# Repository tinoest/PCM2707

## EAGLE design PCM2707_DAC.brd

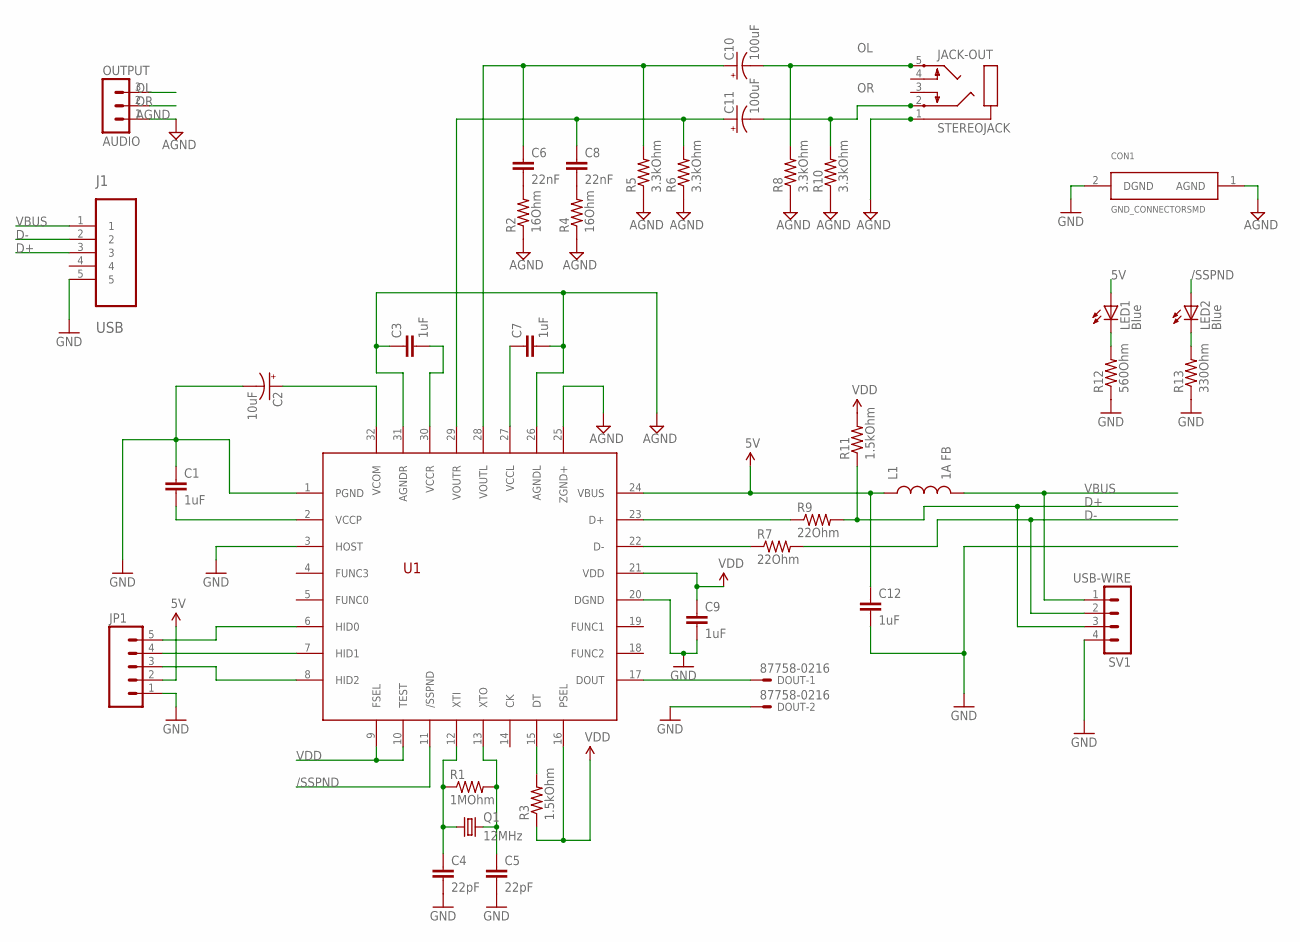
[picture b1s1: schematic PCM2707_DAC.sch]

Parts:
C1, C3, C7, C9, C12: 1uF; 0805
C2: 10uF; PANASONIC_C
C4, C5: 22pF; 0805
C6, C8: 22nF; 1210
C10, C11: 100uF; PANASONIC_D
CON1: GND_CONNECTORSMD; GND_CONNECTOR
DOUT: 87758-0216
J1: USB; MOLEX_47346-0001
JACK-OUT: STEREOJACK; STX3100
JP1: M05LOCK; 1X05_LOCK
L1: 1A FB; 0805
LED1, LED2: Blue; LED-0603
OUTPUT: AUDIO; MA03-1
Q1: 12MHz; HC49U-V
R1: 1MOhm; 0805
R2, R4: 16Ohm; 0805
R3, R11: 1.5kOhm; 0805
R5, R6, R8, R10: 3.3kOhm; 0805
R7, R9: 22Ohm; 0805
R12: 560Ohm; 0805
R13: 330Ohm; 0805
SV1: USB-WIRE; MA04-1
U1: PCM2707C_TQFP32"; 32TQFP_PCM2707C

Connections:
5V: C12.1, JP1.2, L1.1, LED1.A, U1.24 (VBUS)
/SSPND: LED2.A, U1.11 (/SSPND)
AGND: C3.1, C7.2, CON1.1 (AGND), JACK-OUT.1, OUTPUT.1, R2.1, R4.1, R5.1, R6.1, R8.1, R10.1, U1.25 (ZGND+), U1.26 (AGNDL), U1.31 (AGNDR)
D+: J1.3, R9.2, R11.1, SV1.3
D-: J1.2, R7.2, SV1.2
GND: C1.1, C2.-, C4.2, C5.2, C9.2, C12.2, CON1.2 (DGND), DOUT.2, J1.5, JP1.1, R12.1, R13.1, SV1.4, U1.1 (PGND), U1.3 (HOST), U1.20 (DGND)
unnamed: JP1.5, U1.6 (HID0)
unnamed: C1.2, U1.2 (VCCP)
unnamed: JP1.4, U1.7 (HID1)
unnamed: C2.+, U1.32 (VCOM)
unnamed: JP1.3, U1.8 (HID2)
unnamed: DOUT.1, U1.17 (DOUT)
unnamed: C4.1, Q1.1, R1.1, U1.12 (XTI)
unnamed: C5.1, Q1.2, R1.2, U1.13 (XTO)
unnamed: R9.1, U1.23 (D+)
unnamed: R7.1, U1.22 (D-)
unnamed: C3.2, U1.30 (VCCR)
unnamed: LED1.C, R12.2
unnamed: R3.2, U1.15 (DT)
unnamed: C7.1, U1.27 (VCCL)
unnamed: C8.2, R4.2
unnamed: C6.2, R2.2
unnamed: C8.1, C11.+, R6.2, U1.29 (VOUTR)
unnamed: LED2.C, R13.2
unnamed: C6.1, C10.+, R5.2, U1.28 (VOUTL)
OL: C10.-, JACK-OUT.5, OUTPUT.3, R8.2
OR: C11.-, JACK-OUT.2, OUTPUT.2, R10.2
VBUS: J1.1, L1.2, SV1.1
VDD: C9.1, R3.1, R11.2, U1.9 (FSEL), U1.10 (TEST), U1.16 (PSEL), U1.21 (VDD)

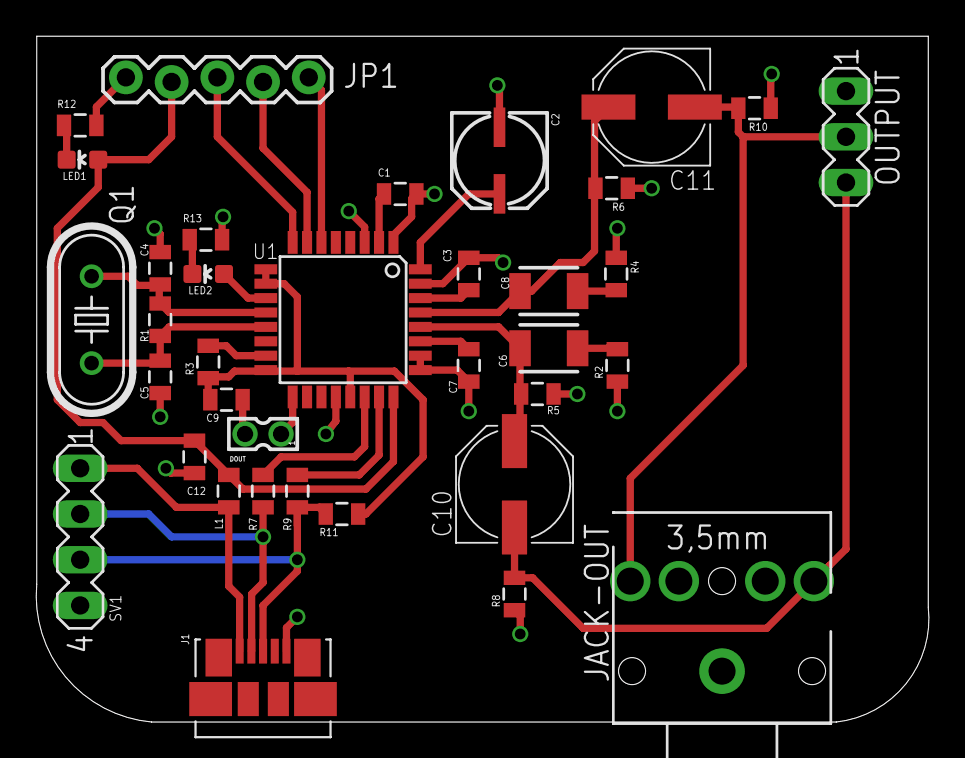
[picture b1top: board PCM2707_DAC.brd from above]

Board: 2 copper layers, 49.6 x 38.1 mm, 37 parts (1 on the bottom side), 29 nets.

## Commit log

2016-12-10 PCM2707 DAC Design
    Simple first check in of logic
2017-03-19 Added Gerber Files
    Created Gerber Data
2017-03-19 Added updated files, and PDF of data
2017-03-19 Added Component List
2017-03-24 Adding kicad files
2017-03-25 Added MOD file
2017-03-25 Modified kicad files and corrected errors
2017-03-25 Modified and matched footprints
2017-03-25 Updated Schematic to use exported Eagle lbw
2017-03-25 Adding modified files
2017-03-25 Tidied up names, corrected PCB footprint
2017-03-25 Removed not required .lbr
2017-03-25 Removed library prefix from library files
2017-03-25 Rounded corners on design, adding kicad generated berbers
2017-03-25 Revert "Rounded corners on design, adding kicad generated berbers"
    This reverts commit da9f95aa9fce01ce657d28d8956f70ecfce44641.
2017-03-25 Revert "Revert "Rounded corners on design, adding kicad generated gerbers""
    This reverts commit e5d359f14d2e2aadcde64fe7d354a7193523fc92.
2017-04-07 Corrected Crystal Part #
2017-11-08 Converted Libs
    Converted PCM2707 libs from legacy to new version
2017-11-08 Removed .txt and .bak files
2017-11-08 Moved zip of gerbers to gerbers folder
2020-05-16 Updated gitignore

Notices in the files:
parts and their libraries:
SparkFun-Passives: Licensing: Creative Commons ShareAlike 4.0 International - https://creativecommons.org/licenses/by-sa/4.0
